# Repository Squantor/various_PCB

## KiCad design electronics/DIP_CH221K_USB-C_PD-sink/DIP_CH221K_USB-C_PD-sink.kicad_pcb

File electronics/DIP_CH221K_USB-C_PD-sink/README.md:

# DIP module CH221K USB-C PD sink
This is a USB-C PD sink using a CH221K chip in DIP format.
## TODO's
Still some things need to be done:
* Review with one night in between
* Produce at [Aisler](https://aisler.net/)
* Assemble
* Test & characterise
* update Readme.md with pictures and BOM
## BOM
 or LCSC
* CH221K USB-C PD sink
* USB-C connector PD only

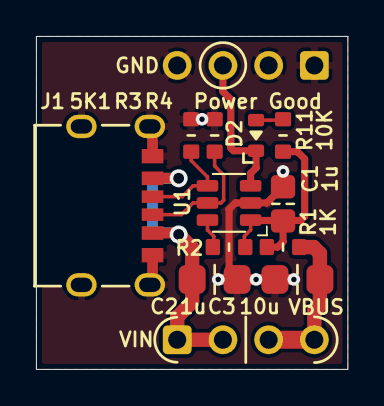
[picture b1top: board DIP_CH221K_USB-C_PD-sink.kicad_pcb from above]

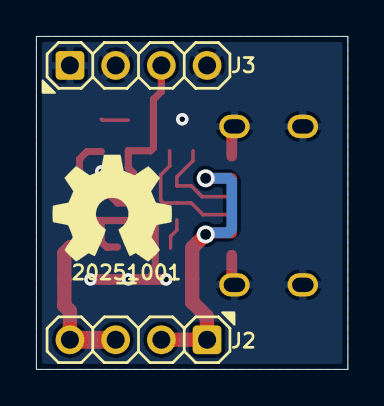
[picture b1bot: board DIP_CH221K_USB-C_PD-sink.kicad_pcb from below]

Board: 2 copper layers, 17.3 x 18.5 mm, 15 parts (4 on the bottom side), 9 nets.

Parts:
C1: 1u; C_0805+0603
C2: 1u; C_1206_0805
C3: 10u; C_1206_0805
D2: Power Good; LED_0603_hand
J1: USB-C_PD; USB-C-HRO-31-M-17_aisler
J2, J3: Conn_01x04; Header-0254-1X04-H010
N1: 20251001; Label_Generic
N2: OHWLOGO; OSHW-Symbol_6.7x6mm_SilkScreen
R1: 1K; R_0603_hand
R2: RSET; R_0603_hand
R3, R4: 5K1; R_0603_hand
R11: 10K; R_0603_hand
U1: CH221K; SOT23-6-HAND

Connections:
/CC1: J1.A5 (CC1), R3.1, U1.4 (CC1)
/CC2: J1.B5 (CC2), R4.1, U1.5 (CC2)
/PG: D2.1 (K), J3.3, U1.3 (PG)
/VBUS: C3.1, J2.3, J2.4, R1.1
/VDD: C1.2, R1.2, R2.2, R11.1, U1.1 (VDD)
/VIN: C2.1, J1.A9 (VBUS), J1.B9 (VBUS), J2.1, J2.2
GND: C1.1, C2.2, C3.2, J1.A12 (GND), J1.B12 (GND), J1.S (Shield), J3.1, J3.2, J3.4, R3.2, R4.2, U1.2 (GND)
unnamed: D2.2 (A), R11.2
unnamed: R2.1, U1.6 (CFG)

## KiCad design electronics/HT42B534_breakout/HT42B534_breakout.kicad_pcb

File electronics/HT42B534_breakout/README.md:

# Holtek HT42B534 breakout board
Breakout board for the [HT42B534-1](https://www.holtek.com/productdetail/-/vg/42B534-x) USB to serial converter. Advantage of the HT42B534 is that it enumerates as a USB CDC device, has programmable EEPROM on board and available in a few tiny packages.
## TODO's
Still some things need to be done:
* schematic entry
* PCB layout
* Review with one night in between (TODO)
* Produce at [OSHPARK](https://oshpark.com/) (TODO)
* Assemble (TODO)
* Test & characterise (TODO)
* update Readme.md with pictures and BOM (TODO)
## BOM
The HT42B534 can be hard to find but is available from [LCSC](https://lcsc.com/.
* HT42B534-1, [C95344 from LCSC](https://lcsc.com/product-detail/USB_HT42B534-MSOP-10_C95344.html)

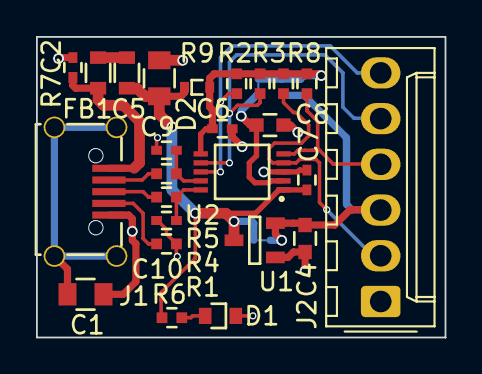
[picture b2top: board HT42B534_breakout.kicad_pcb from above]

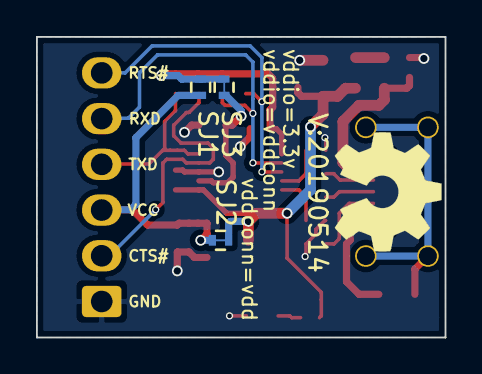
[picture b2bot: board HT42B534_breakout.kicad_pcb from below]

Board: 2 copper layers, 22.7 x 16.7 mm, 30 parts (5 on the bottom side), 18 nets.

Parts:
C1: 100n; C_0805
C2, C6, C7: 100n; C_0402
C4, C8: 1u; C_0603
C5: 10u; C_0805
C9, C10: 47p; C_0402
D1: RED; D_0603_hand
D2: D_Schottky; SOD-523
FB1: 600; R_0603_hand
J1: USB-ID; USB-muB-SMD_TH
J2: FTDI_PINS_1X06_input; Molex_KK-254_AE-6410-06A_1x06_P2.54mm_Vertical_FTDI_UART
N1: OHWLOGO; OSHW-Symbol_6.7x6mm_SilkScreen
N2: 20190514; Label_version
R1: 0; R_0402_hand
R2, R3, R8, R9: 10K; R_0402_hand
R4, R5: 33; R_0402_hand
R6: 1K; R_0402_hand
R7: Fuse; R_0603_hand
SJ1: vddio=vddconn; solder_jumper_2way_noconn
SJ2: vddconn=vdd; solder_jumper_2way_conn
SJ3: vddio=3.3v; solder_jumper_2way_conn
U1: MCP1702-CB; SOT23-3-Microchip-TT
U2: HT42B534-MSOP10; MSOP-10

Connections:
/CTSI: J2.2, R3.1, U2.4
/RTSO: J2.6, R9.1, U2.8
/RXI: J2.5, R2.1, U2.7
/TXO: J2.4, R8.1, U2.5
/USB_DM: J1.2, R5.1
/USB_DP: J1.3, R4.1
/VBUS: C2.1, J1.1, R7.2
/VDD: C5.1, C7.1, D2.1, FB1.1, R6.2, SJ2.2, U1.3, U2.1
/VDDCONN: C4.1, J2.3, SJ1.1, SJ2.1, U1.2
/VDDIO: C6.1, D2.2, R2.2, R3.2, R8.2, R9.2, SJ1.2, SJ3.1, U2.6
/VDD_33V: C8.1, SJ3.2, U2.2
/VSS: C1.2, C2.2, C4.2, C5.2, C6.2, C7.2, C8.2, C9.1, C10.1, D1.1, J1.5, J2.1, R1.2, U1.1, U2.3
unnamed: C1.1, J1.S
unnamed: C9.2, R5.2, U2.9
unnamed: C10.2, R4.2, U2.10
unnamed: D1.2, R6.1
unnamed: FB1.2, R7.1
unnamed: J1.4, R1.1

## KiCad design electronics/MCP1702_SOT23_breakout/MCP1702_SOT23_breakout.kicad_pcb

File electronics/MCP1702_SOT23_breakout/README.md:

# MCP1702 SOT23 breakout
Simple breakout for the SOT23 packaged MCP1702
## TODO's
Still some things need to be done:
* Produce at [OSHPARK](https://oshpark.com/shared_projects/U77scmmd) (WIP)
* Assemble (TODO)
* Test & characterise (TODO)
* update Readme.md with pictures and BOM (TODO)
## BOM
Due to the general shortage of passive components, where mentioned, just whatever you can find.
* [MCP1702](http://ww1.microchip.com/downloads/en/DeviceDoc/22008E.pdf)
Dual 0805/0603 footprint present to accomodate a few capacitor types.

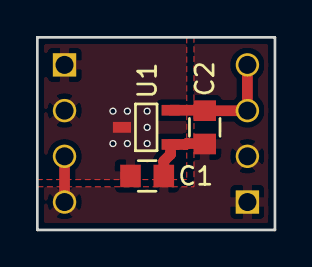
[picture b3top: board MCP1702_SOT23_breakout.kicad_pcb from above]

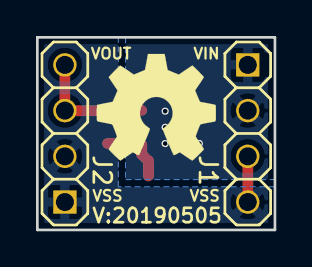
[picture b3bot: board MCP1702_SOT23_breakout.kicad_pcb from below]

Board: 2 copper layers, 13.2 x 10.7 mm, 7 parts (3 on the bottom side), 3 nets.

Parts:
C1, C2: TBD; C_0805+0603
J1: reference_input
J2: reference_output
N1: OHWLOGO; OSHW-Symbol_6.7x6mm_SilkScreen
N2: 20190505; Label_version
U1: MCP1702-CB; SOT23-3-Microchip-CB

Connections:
/VIN: C1.2, J1.1, J1.2, U1.3
/VOUT: C2.1, J2.3, J2.4, U1.2
/VSS: C1.1, C2.2, J1.3, J1.4, J2.1, J2.2, U1.1

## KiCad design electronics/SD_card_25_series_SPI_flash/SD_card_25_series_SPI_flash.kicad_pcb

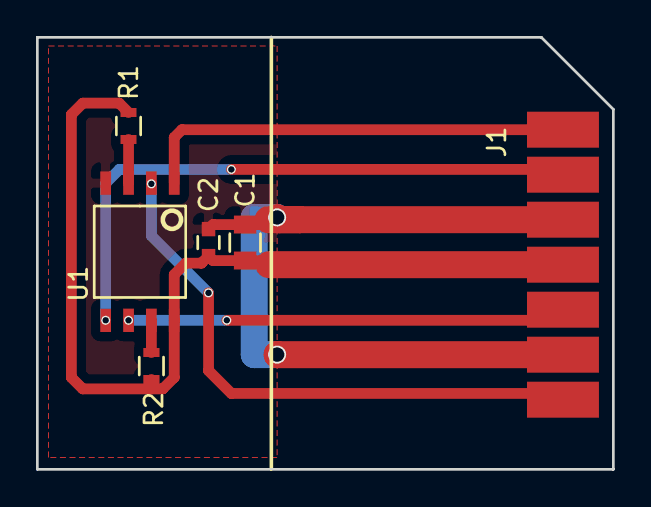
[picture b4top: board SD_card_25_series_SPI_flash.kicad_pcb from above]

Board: 2 copper layers, 32.0 x 24.0 mm, 6 parts (0 on the bottom side), 8 nets.

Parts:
C1: 1u; C_0805
C2: 100n; C_0603
J1: SD_CARD_connector
R1: 10K; R_0603
R2: 10k; R_0603
U1: W25Q32BV; W25Q32BVST

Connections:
+3V3: C1.1, C2.1, J1.4, R1.2, R2.1, U1.8
CS: J1.1, U1.1
DI: J1.2, U1.5
DO: J1.7, U1.2
GND: C1.2, C2.2, J1.3, J1.6, U1.4
unnamed: R1.1, U1.3
unnamed: R2.2, U1.7
SCLK: J1.5, U1.6

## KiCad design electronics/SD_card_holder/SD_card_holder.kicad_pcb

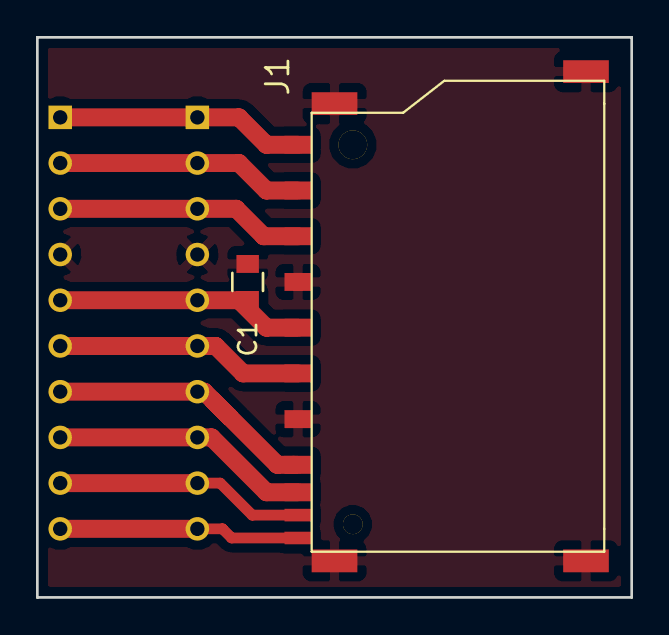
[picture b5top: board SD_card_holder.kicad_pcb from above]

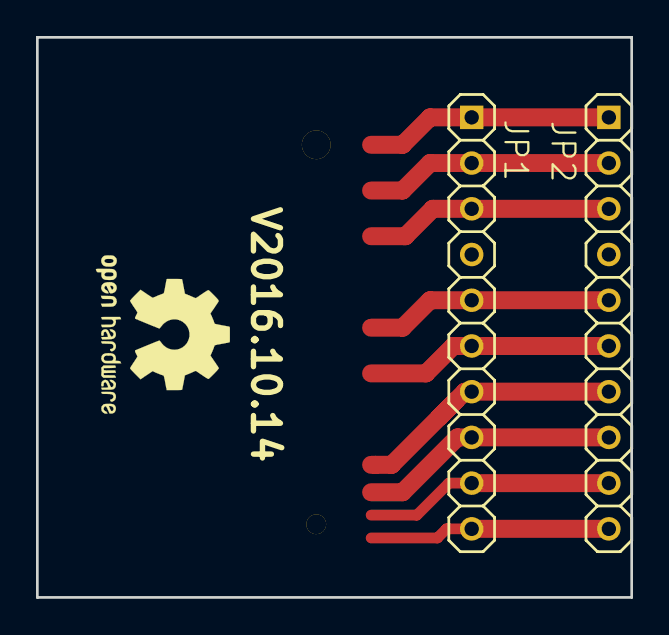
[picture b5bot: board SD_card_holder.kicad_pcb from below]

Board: 2 copper layers, 33.0 x 31.1 mm, 4 parts (2 on the bottom side), 10 nets.

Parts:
C1: 1u; C_0805
J1: SDCMF-10915W010; SquantorConnectors-SDCMF-10915W010
JP1, JP2: PINHD-1X10TH_NORMAL; SquantorConnectors-1X10_SMALL

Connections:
+3V3: C1.1, J1.4, JP1.5, JP2.5
GND: C1.2, J1.3, J1.6, J1.S1, J1.S2, J1.S3, J1.S4, JP1.4, JP2.4
unnamed: J1.1, JP1.2, JP2.2
unnamed: J1.2, JP1.3, JP2.3
unnamed: J1.5, JP1.6, JP2.6
unnamed: J1.7, JP1.7, JP2.7
unnamed: J1.8, JP1.8, JP2.8
unnamed: J1.9, JP1.1, JP2.1
unnamed: J1.CD, JP1.9, JP2.9
unnamed: J1.WP, JP1.10, JP2.10

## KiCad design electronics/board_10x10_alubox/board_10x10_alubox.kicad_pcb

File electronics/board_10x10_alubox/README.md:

# 4 module mainboard for 10*10cm aluminium box
Mainboard capable of fitting 4 5*4cm modules
# HSI (Hardware Software Interface)
TODO
## TODO's
Still some things need to be done:
* schematic entry 
* PCB layout
* Review with one night in between
* Produce at [OSHPARK](https://oshpark.com/)
* Assemble
* Test & characterise
* update Readme.md with pictures and BOM

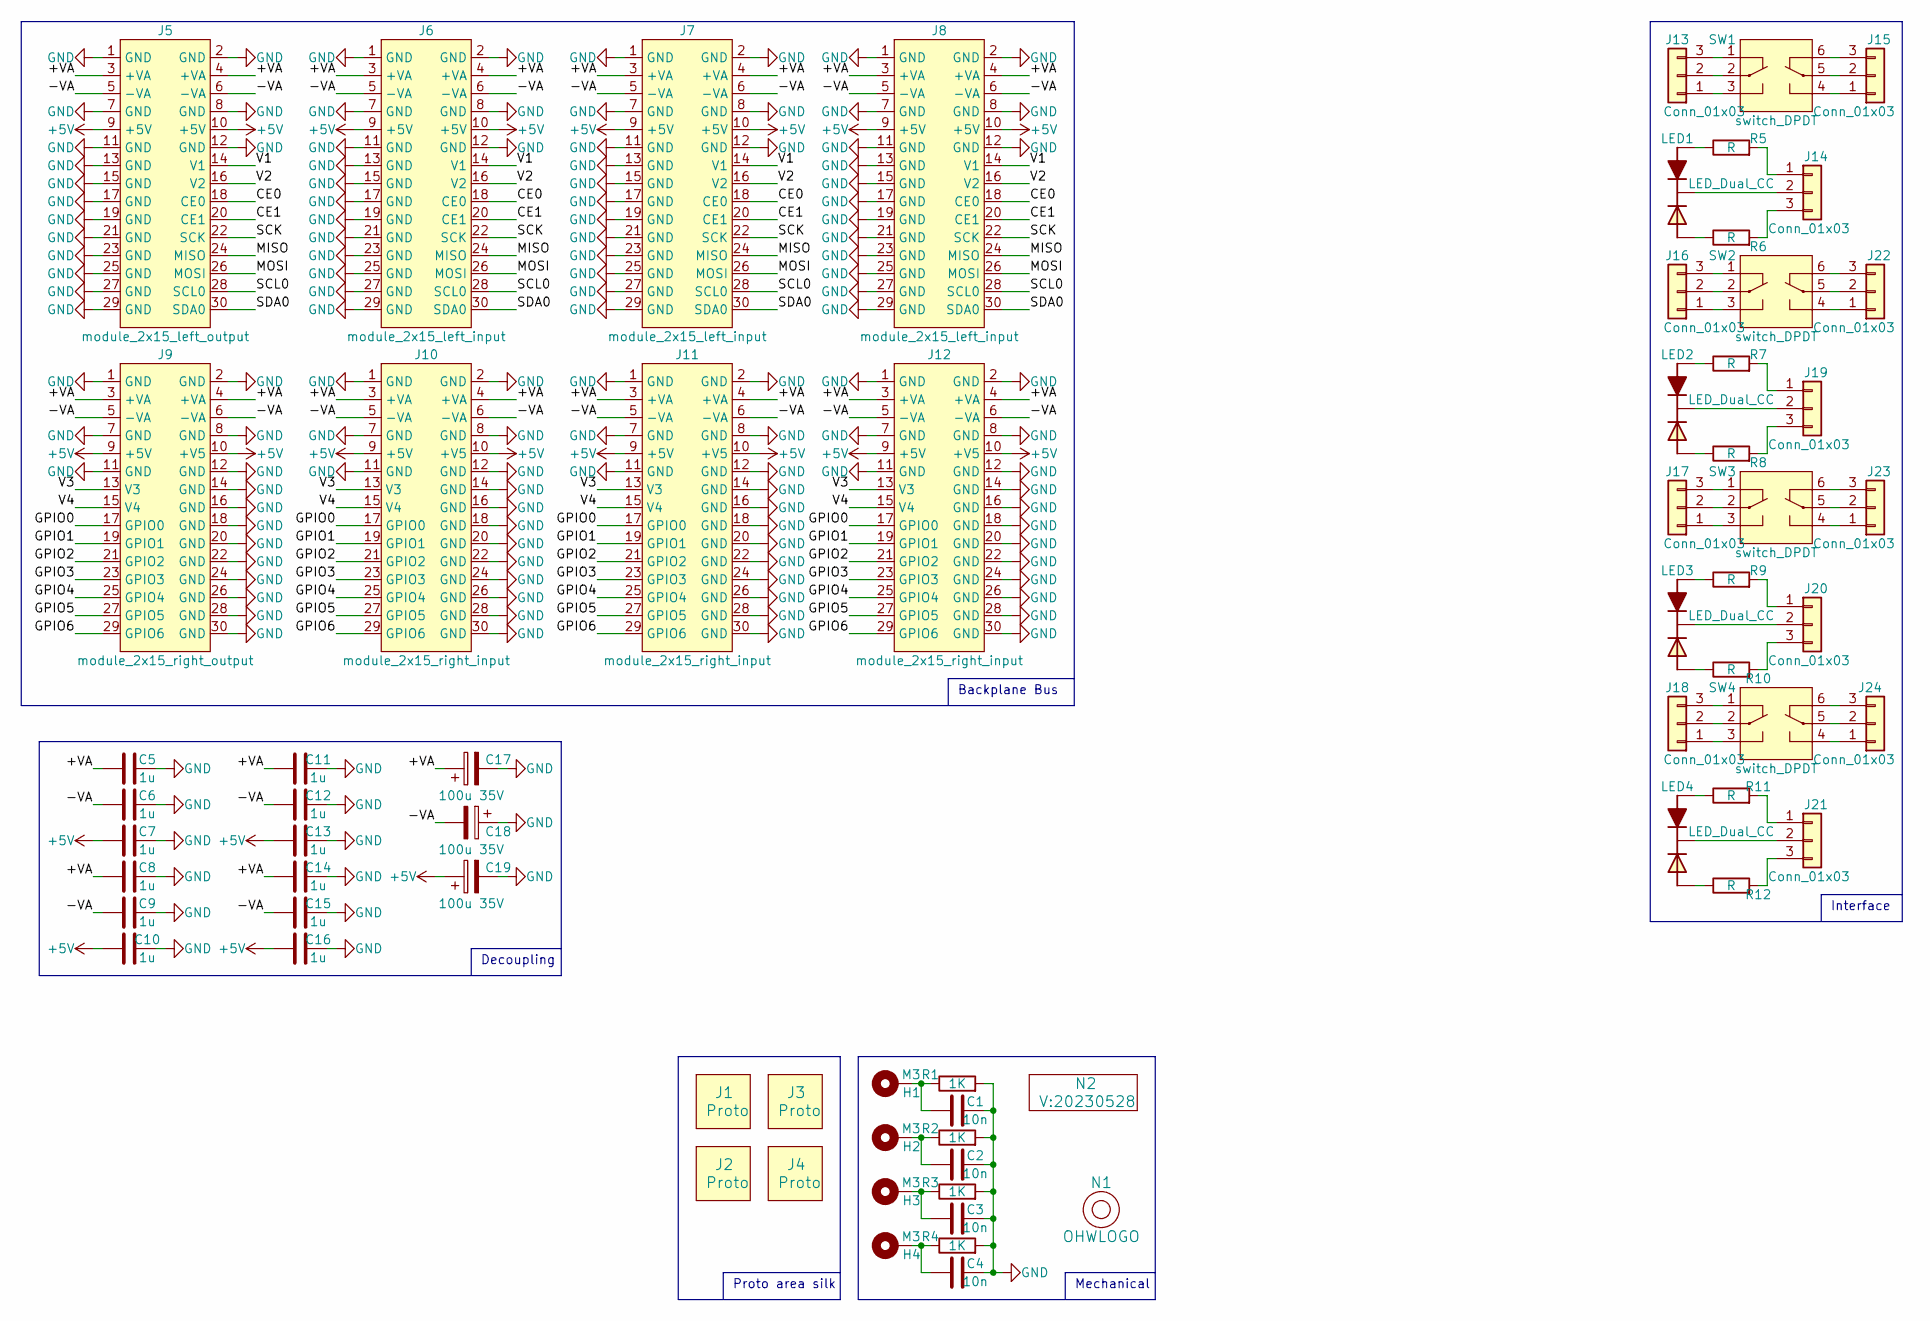
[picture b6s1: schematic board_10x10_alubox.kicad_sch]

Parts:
C1, C2, C3, C4: 10n; C_0805+0603
C5, C6, C7, C8, C9, C10, C11, C12, C13, C14, C15, C16: 1u; C_0805+0603
C17: 100u 35V; C-horizontal-035-080-200-elco-flipped
C18, C19: 100u 35V; C-horizontal-035-080-200-elco
H1, H2, H3, H4: M3; MountingHole_3.2mm_M3_Pad_Via
J1, J2, J3, J4: Proto; 4by4cm_module
J5: module_2x15_left_output; module_2x15_left
J6, J7, J8: module_2x15_left_input; module_2x15_left
J9: module_2x15_right_output; module_2x15_right
J10, J11, J12: module_2x15_right_input; module_2x15_right
J13, J14, J15, J16, J17, J18, J19, J20, J21, J22, J23, J24: Conn_01x03; JST_PH_B3B-PH-K_1x03_P2.00mm_Vertical
LED1, LED2, LED3, LED4: LED_Dual_CC; LED_DUAL_TH245_90deg
N1: OHWLOGO; OSHW-Symbol_6.7x6mm_SilkScreen
N2: V:20230528; Label_Generic
R1, R2, R3, R4: 1K; R_0805+0603
R5, R6, R7, R8, R9, R10, R11, R12: R; R_0603_hand
SW1, SW2, SW3, SW4: switch_DPDT; PS-22F02

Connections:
+5V: C7.1, C10.1, C13.1, C16.1, C19.1, J5.9 (+5V), J5.10 (+5V), J6.9 (+5V), J6.10 (+5V), J7.9 (+5V), J7.10 (+5V), J8.9 (+5V), J8.10 (+5V), J9.9 (+5V), J9.10 (+V5), J10.9 (+5V), J10.10 (+V5), J11.9 (+5V), J11.10 (+V5), J12.9 (+5V), J12.10 (+V5)
/+VA: C5.1, C8.1, C11.1, C14.1, C17.1, J5.3 (+VA), J5.4 (+VA), J6.3 (+VA), J6.4 (+VA), J7.3 (+VA), J7.4 (+VA), J8.3 (+VA), J8.4 (+VA), J9.3 (+VA), J9.4 (+VA), J10.3 (+VA), J10.4 (+VA), J11.3 (+VA), J11.4 (+VA), J12.3 (+VA), J12.4 (+VA)
/-VA: C6.1, C9.1, C12.1, C15.1, C18.2, J5.5 (-VA), J5.6 (-VA), J6.5 (-VA), J6.6 (-VA), J7.5 (-VA), J7.6 (-VA), J8.5 (-VA), J8.6 (-VA), J9.5 (-VA), J9.6 (-VA), J10.5 (-VA), J10.6 (-VA), J11.5 (-VA), J11.6 (-VA), J12.5 (-VA), J12.6 (-VA)
/CE0: J5.18 (CE0), J6.18 (CE0), J7.18 (CE0), J8.18 (CE0)
/CE1: J5.20 (CE1), J6.20 (CE1), J7.20 (CE1), J8.20 (CE1)
/GPIO0: J9.17 (GPIO0), J10.17 (GPIO0), J11.17 (GPIO0), J12.17 (GPIO0)
/GPIO1: J9.19 (GPIO1), J10.19 (GPIO1), J11.19 (GPIO1), J12.19 (GPIO1)
/GPIO2: J9.21 (GPIO2), J10.21 (GPIO2), J11.21 (GPIO2), J12.21 (GPIO2)
/GPIO3: J9.23 (GPIO3), J10.23 (GPIO3), J11.23 (GPIO3), J12.23 (GPIO3)
/GPIO4: J9.25 (GPIO4), J10.25 (GPIO4), J11.25 (GPIO4), J12.25 (GPIO4)
/GPIO5: J9.27 (GPIO5), J10.27 (GPIO5), J11.27 (GPIO5), J12.27 (GPIO5)
/GPIO6: J9.29 (GPIO6), J10.29 (GPIO6), J11.29 (GPIO6), J12.29 (GPIO6)
/MISO: J5.24 (MISO), J6.24 (MISO), J7.24 (MISO), J8.24 (MISO)
/MOSI: J5.26 (MOSI), J6.26 (MOSI), J7.26 (MOSI), J8.26 (MOSI)
/SCK: J5.22 (SCK), J6.22 (SCK), J7.22 (SCK), J8.22 (SCK)
/SCL0: J5.28 (SCL0), J6.28 (SCL0), J7.28 (SCL0), J8.28 (SCL0)
/SDA0: J5.30 (SDA0), J6.30 (SDA0), J7.30 (SDA0), J8.30 (SDA0)
/V1: J5.14 (V1), J6.14 (V1), J7.14 (V1), J8.14 (V1)
/V2: J5.16 (V2), J6.16 (V2), J7.16 (V2), J8.16 (V2)
/V3: J9.13 (V3), J10.13 (V3), J11.13 (V3), J12.13 (V3)
/V4: J9.15 (V4), J10.15 (V4), J11.15 (V4), J12.15 (V4)
GND: C1.2, C2.2, C3.2, C4.2, C5.2, C6.2, C7.2, C8.2, C9.2, C10.2, C11.2, C12.2, C13.2, C14.2, C15.2, C16.2, C17.2, C18.1, C19.2, J5.1 (GND), J5.2 (GND), J5.7 (GND), J5.8 (GND), J5.11 (GND), J5.12 (GND), J5.13 (GND), J5.15 (GND), J5.17 (GND), J5.19 (GND), J5.21 (GND), J5.23 (GND), J5.25 (GND), J5.27 (GND), J5.29 (GND), J6.1 (GND), J6.2 (GND), J6.7 (GND), J6.8 (GND), J6.11 (GND), J6.12 (GND), J6.13 (GND), J6.15 (GND), J6.17 (GND), J6.19 (GND), J6.21 (GND), J6.23 (GND), J6.25 (GND), J6.27 (GND), J6.29 (GND), J7.1 (GND), J7.2 (GND), J7.7 (GND), J7.8 (GND), J7.11 (GND), J7.12 (GND), J7.13 (GND), J7.15 (GND), J7.17 (GND), J7.19 (GND), J7.21 (GND), J7.23 (GND), J7.25 (GND), J7.27 (GND), J7.29 (GND), J8.1 (GND), J8.2 (GND), J8.7 (GND), J8.8 (GND), J8.11 (GND), J8.12 (GND), J8.13 (GND), J8.15 (GND), J8.17 (GND), J8.19 (GND), J8.21 (GND), J8.23 (GND), J8.25 (GND), J8.27 (GND), J8.29 (GND), J9.1 (GND), J9.2 (GND), J9.7 (GND), J9.8 (GND), J9.11 (GND), J9.12 (GND), J9.14 (GND), J9.16 (GND), J9.18 (GND), J9.20 (GND), J9.22 (GND), J9.24 (GND), J9.26 (GND), J9.28 (GND), J9.30 (GND), J10.1 (GND), J10.2 (GND), J10.7 (GND), J10.8 (GND), J10.11 (GND), J10.12 (GND), J10.14 (GND), J10.16 (GND), J10.18 (GND), J10.20 (GND), J10.22 (GND), J10.24 (GND), J10.26 (GND), J10.28 (GND), J10.30 (GND), J11.1 (GND), J11.2 (GND), J11.7 (GND), J11.8 (GND), J11.11 (GND), J11.12 (GND), J11.14 (GND), J11.16 (GND), J11.18 (GND), J11.20 (GND), J11.22 (GND), J11.24 (GND), J11.26 (GND), J11.28 (GND), J11.30 (GND), J12.1 (GND), J12.2 (GND), J12.7 (GND), J12.8 (GND), J12.11 (GND), J12.12 (GND), J12.14 (GND), J12.16 (GND), J12.18 (GND), J12.20 (GND), J12.22 (GND), J12.24 (GND), J12.26 (GND), J12.28 (GND), J12.30 (GND), R1.2, R2.2, R3.2, R4.2
unnamed: C1.1, H1.1, R1.1
unnamed: C2.1, H2.1, R2.1
unnamed: C3.1, H3.1, R3.1
unnamed: C4.1, H4.1, R4.1
unnamed: J13.1, SW1.3 (SW1_P2)
unnamed: J13.2, SW1.2 (SW1_C1)
unnamed: J13.3, SW1.1 (SW1_P1)
unnamed: J14.1, R5.2
unnamed: J14.2, LED1.2 (C)
unnamed: J14.3, R6.2
unnamed: J15.1, SW1.4 (SW2_P2)
unnamed: J15.2, SW1.5 (SW2_C1)
unnamed: J15.3, SW1.6 (SW2_P2)
unnamed: J16.1, SW2.3 (SW1_P2)
unnamed: J16.2, SW2.2 (SW1_C1)
unnamed: J16.3, SW2.1 (SW1_P1)
unnamed: J17.1, SW3.3 (SW1_P2)
unnamed: J17.2, SW3.2 (SW1_C1)
unnamed: J17.3, SW3.1 (SW1_P1)
unnamed: J18.1, SW4.3 (SW1_P2)
unnamed: J18.2, SW4.2 (SW1_C1)
unnamed: J18.3, SW4.1 (SW1_P1)
unnamed: J19.1, R7.2
unnamed: J19.2, LED2.2 (C)
unnamed: J19.3, R8.2
unnamed: J20.1, R9.2
unnamed: J20.2, LED3.2 (C)
unnamed: J20.3, R10.2
unnamed: J21.1, R11.2
unnamed: J21.2, LED4.2 (C)
unnamed: J21.3, R12.2
unnamed: J22.1, SW2.4 (SW2_P2)
unnamed: J22.2, SW2.5 (SW2_C1)
unnamed: J22.3, SW2.6 (SW2_P2)
unnamed: J23.1, SW3.4 (SW2_P2)
unnamed: J23.2, SW3.5 (SW2_C1)
unnamed: J23.3, SW3.6 (SW2_P2)
unnamed: J24.1, SW4.4 (SW2_P2)
unnamed: J24.2, SW4.5 (SW2_C1)
unnamed: J24.3, SW4.6 (SW2_P2)
unnamed: LED1.1 (A1), R5.1
unnamed: LED1.3 (A2), R6.1
unnamed: LED2.1 (A1), R7.1
unnamed: LED2.3 (A2), R8.1
unnamed: LED3.1 (A1), R9.1
unnamed: LED3.3 (A2), R10.1
unnamed: LED4.1 (A1), R11.1
unnamed: LED4.3 (A2), R12.1

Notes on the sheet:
Proto area silk
Decoupling
Interface
Mechanical
Backplane Bus

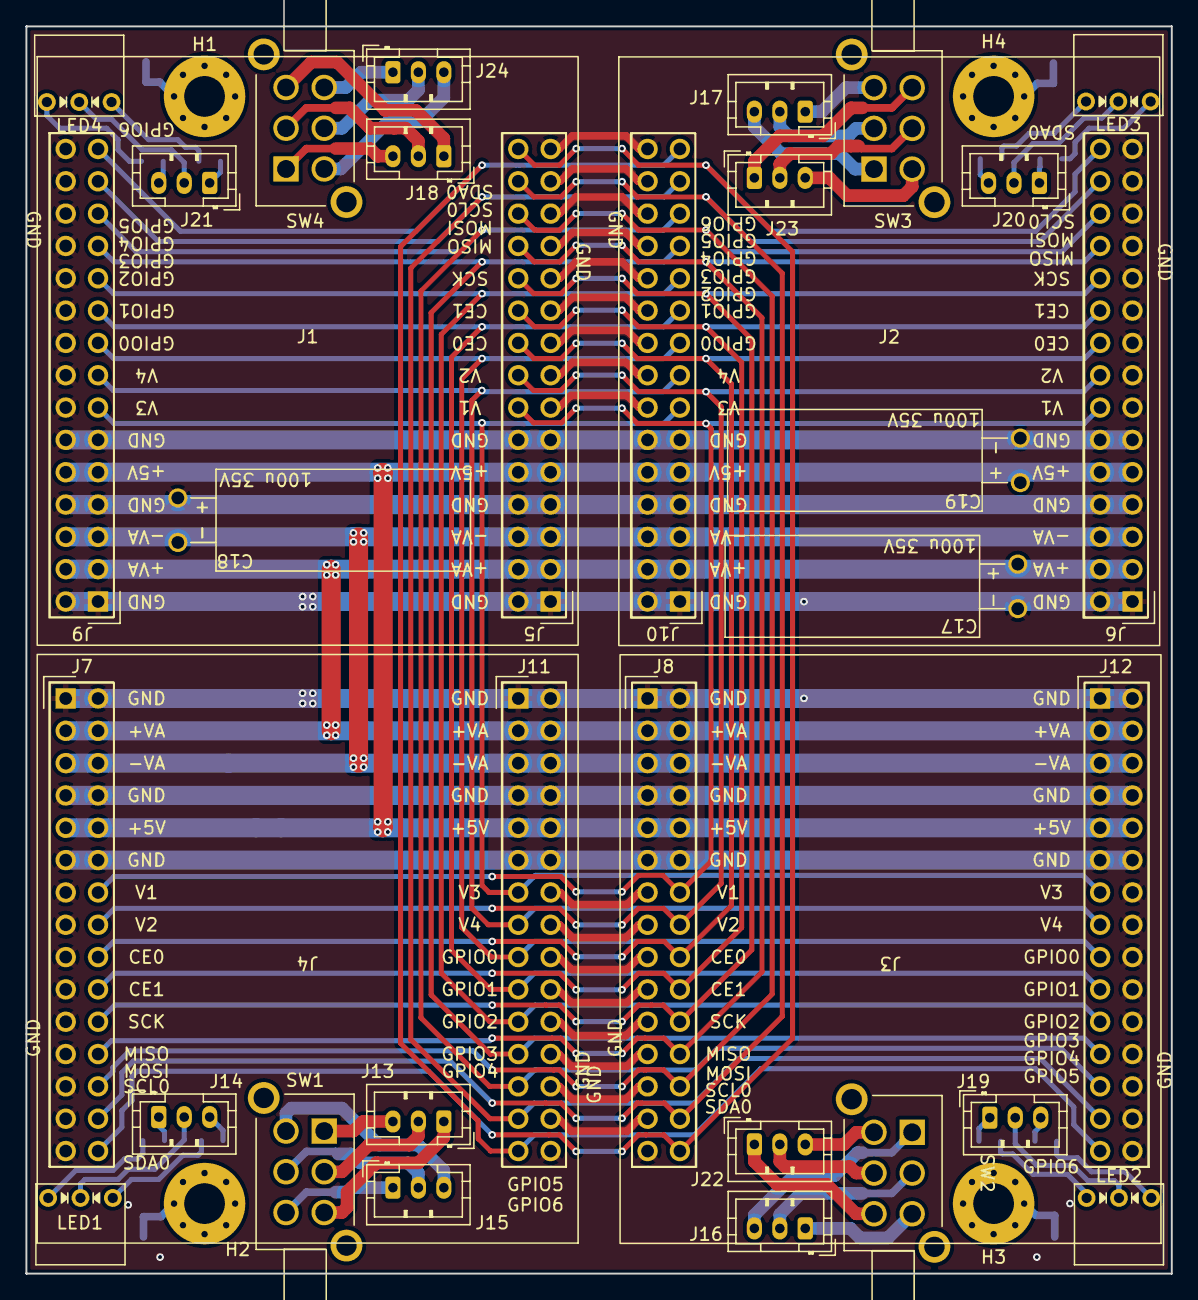
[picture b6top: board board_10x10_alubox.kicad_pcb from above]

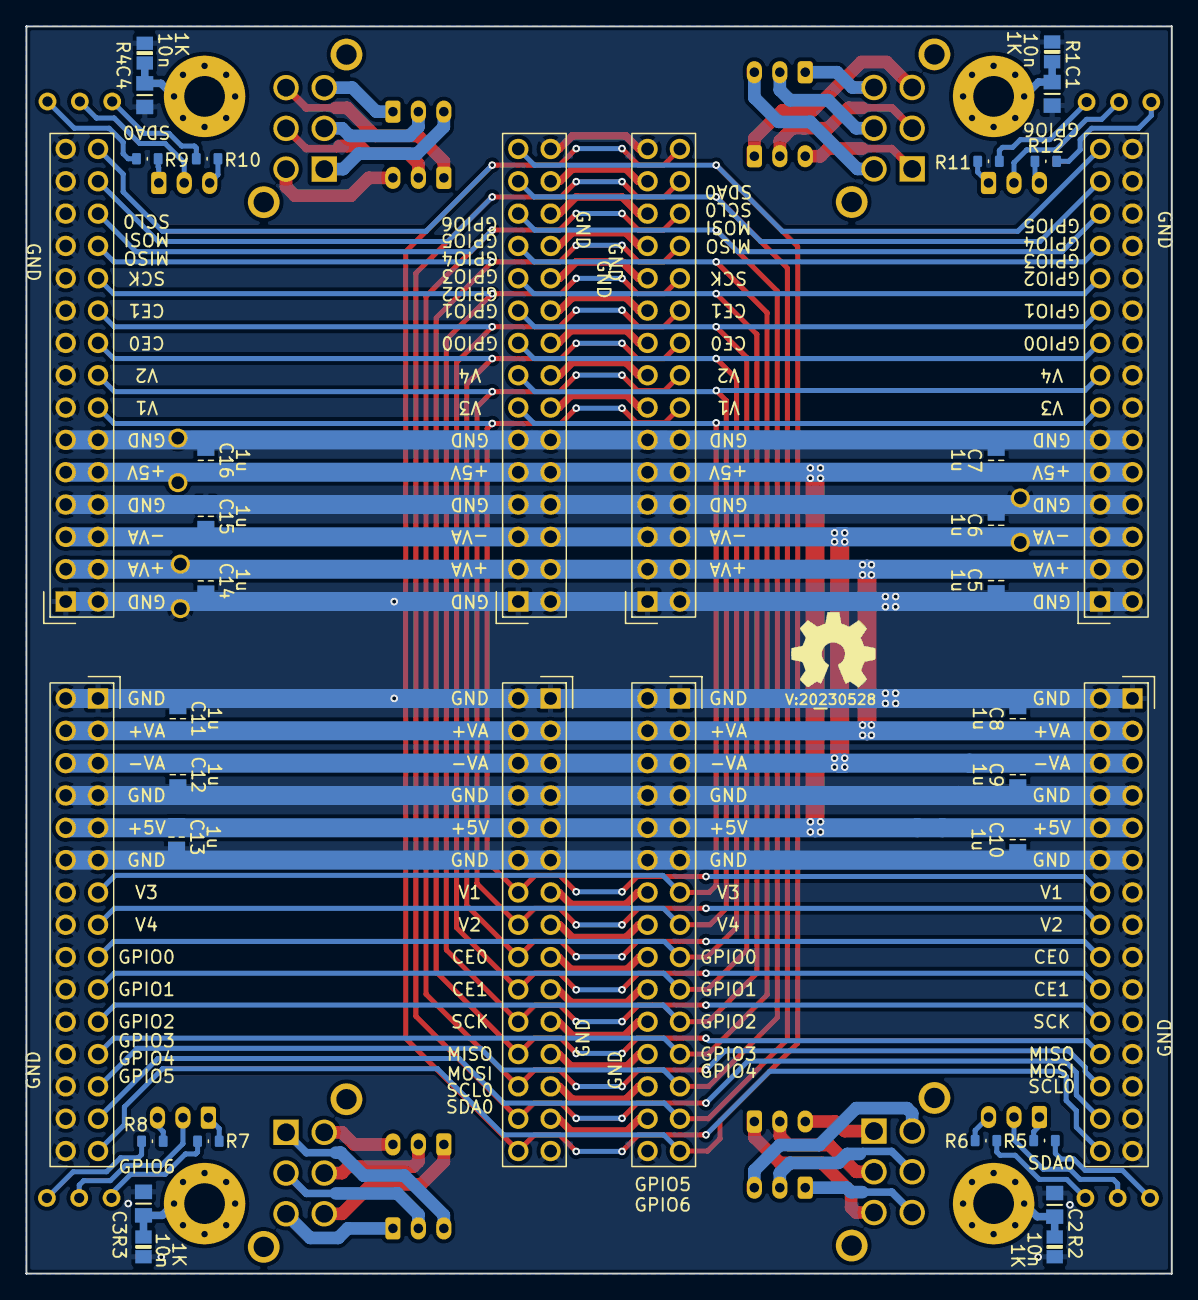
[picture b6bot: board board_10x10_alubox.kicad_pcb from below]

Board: 2 copper layers, 90.0 x 98.0 mm, 69 parts (30 on the bottom side), 70 nets.

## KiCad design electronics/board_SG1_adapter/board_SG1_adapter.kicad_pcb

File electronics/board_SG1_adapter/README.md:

# Strapubox SG1 adapter board template
baseline PCB for the [SG1 adapter box from strapubox](https://www.strapubox.de/wp-content/uploads/2021/06/MB21-0078_Strapubox_DB_Eurostecker_01.pdf).
## TODO's
Still some things need to be done:
* Review with one night in between
* Produce PCB
* Assemble
* Test & characterise
* update Readme.md with pictures and BOM
## BOM
* Standard transformer sizing

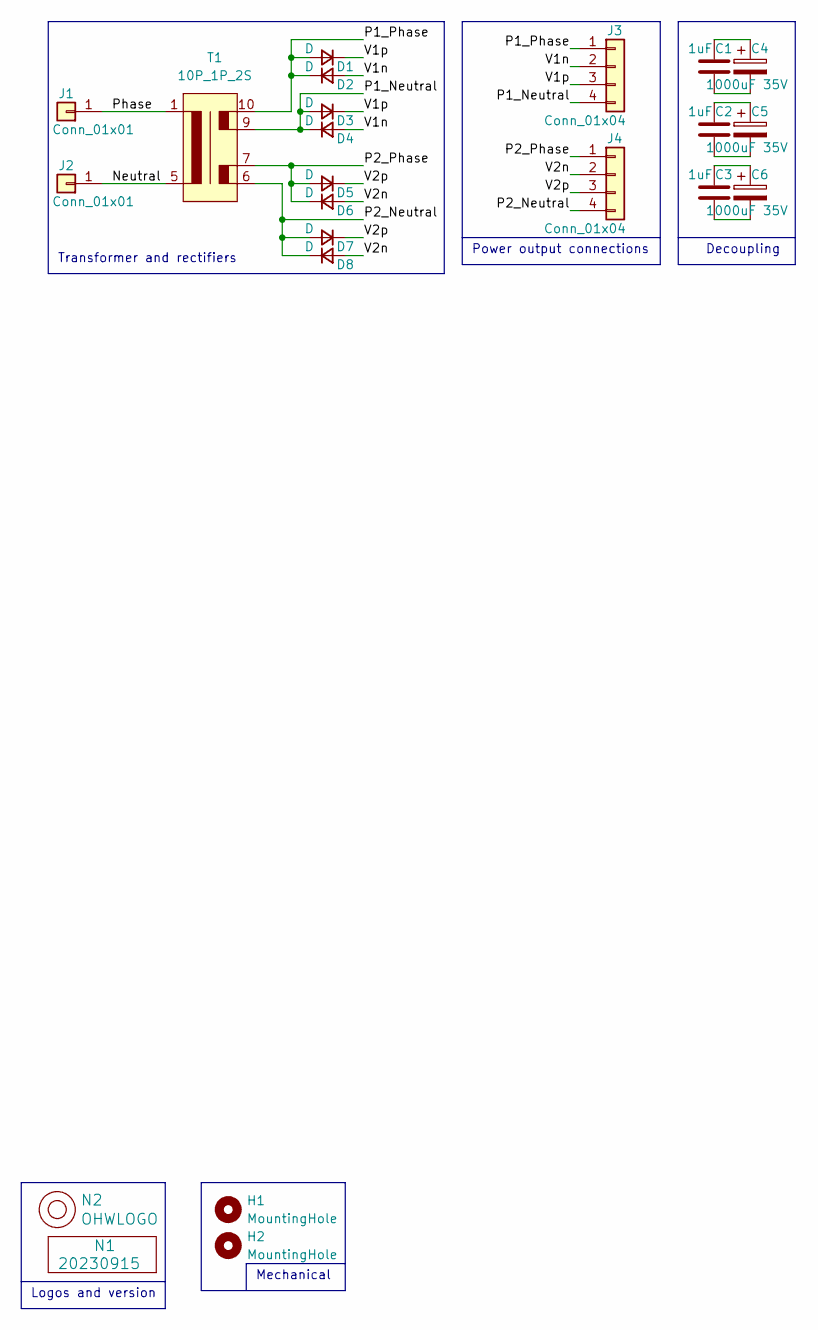
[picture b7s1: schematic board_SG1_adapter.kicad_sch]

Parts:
C1, C2, C3: 1uF; C_0805+0603
C4, C5, C6: 1000uF 35V; C-050-100-elco
D1, D2, D3, D4, D5, D6, D7, D8: D; D_SMB
H1, H2: MountingHole; MountingHole_2.2mm_M2
J1, J2: Conn_01x01; pad_power
J3, J4: Conn_01x04; JST_XH_B4B-XH-A_1x04_P2.50mm_Vertical
N1: 20230915; Label_Generic
N2: OHWLOGO; OSHW-Symbol_6.7x6mm_SilkScreen
T1: 10P_1P_2S; 10pin_5pitch_32x27_1Pri_2Sec

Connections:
/Neutral: J2.1, T1.5
/P1_Neutral: D3.2 (A), D4.1 (K), J3.4, T1.9
/P1_Phase: D1.2 (A), D2.1 (K), J3.1, T1.10
/P2_Neutral: D7.2 (A), D8.1 (K), J4.4, T1.6
/P2_Phase: D5.2 (A), D6.1 (K), J4.1, T1.7
/Phase: J1.1, T1.1
/V1n: D2.2 (A), D4.2 (A), J3.2
/V1p: D1.1 (K), D3.1 (K), J3.3
/V2n: D6.2 (A), D8.2 (A), J4.2
/V2p: D5.1 (K), D7.1 (K), J4.3
unnamed: C1.1, C4.1
unnamed: C1.2, C4.2
unnamed: C2.1, C5.1
unnamed: C2.2, C5.2
unnamed: C3.1, C6.1
unnamed: C3.2, C6.2

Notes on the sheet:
Power output connections
Decoupling
Logos and version
Transformer and rectifiers
Mechanical

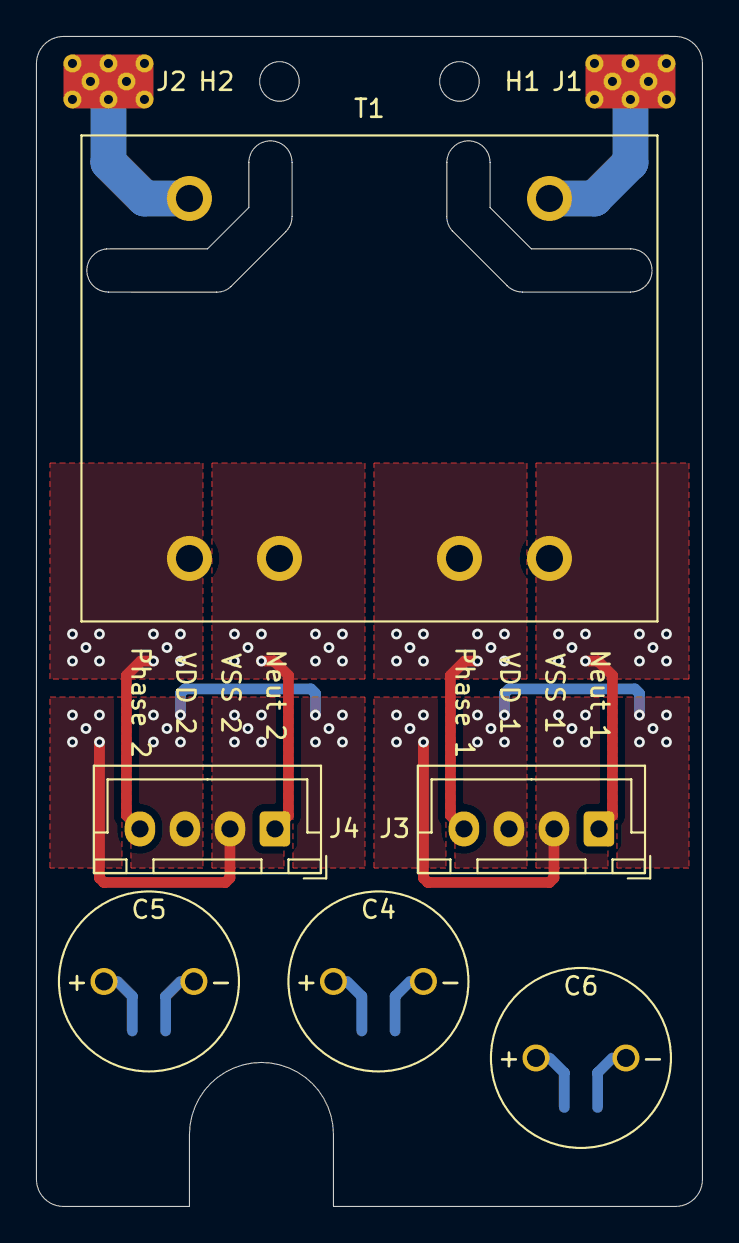
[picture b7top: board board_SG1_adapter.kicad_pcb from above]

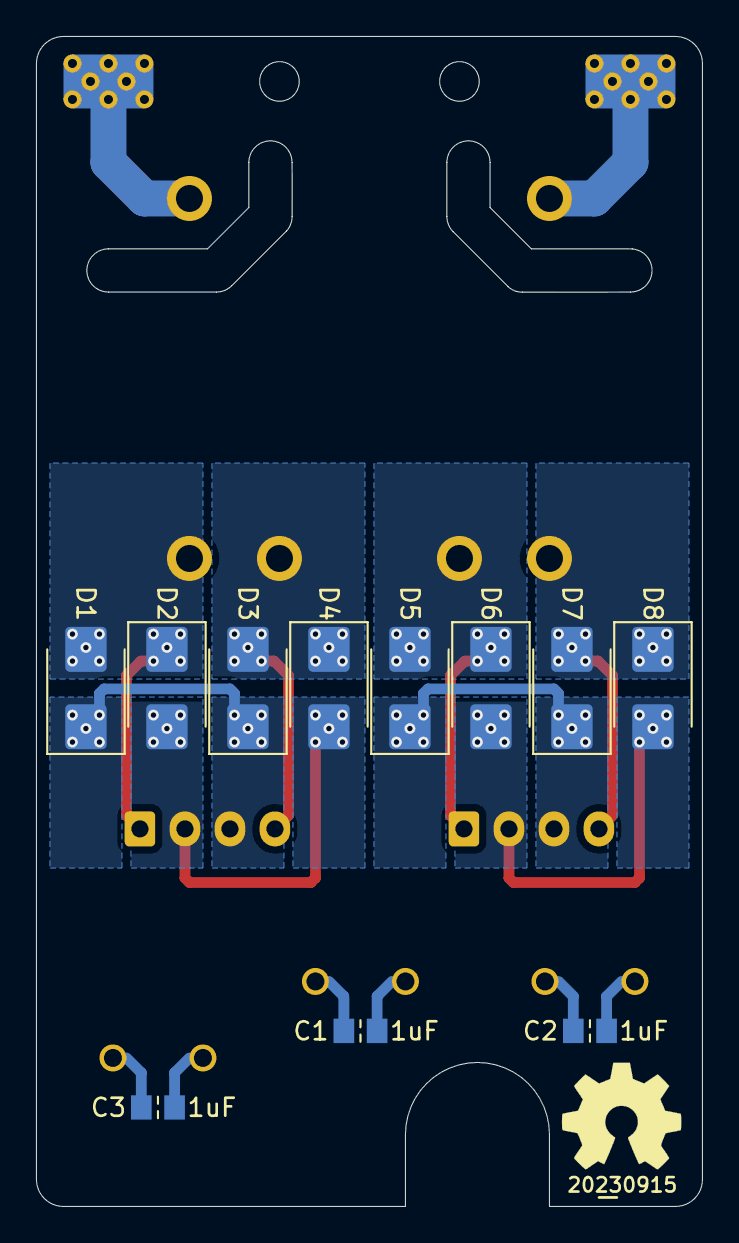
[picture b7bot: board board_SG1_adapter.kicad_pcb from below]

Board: 2 copper layers, 37.0 x 65.0 mm, 23 parts (13 on the bottom side), 16 nets.

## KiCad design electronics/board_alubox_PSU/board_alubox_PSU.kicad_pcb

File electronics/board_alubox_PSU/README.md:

# 10x10cm alubox module powersupply
4 by 5cm module with powersupply components. Two AC inputs one for a symmetrical powersupply and one for a single ended powersupply. Symmetric powersupply accepts LM317/LM337 regulators. Single ended supply has footprints for a LM317 regulator and LM78XX style regulators. All regulators are TO220 with a small heatsink. Due to limited space for capacitance the amount of current is also limited.
## TODO's
Still some things need to be done:
* schematic entry (WIP)
* PCB layout
* Review with one night in between
* Produce at [OSHPARK](https://oshpark.com/)
* Assemble
* Test & characterise
* update Readme.md with pictures and BOM
## BOM
This is a list of hardware components. If just mentioned a generic component like a 1K 0402 resistor, just name it as such, free to substitute. If you need some special integrated IC's show some sources like Mouser, Digikey, Farnell, or LCSC
* TO220 LM317, LM337, LM78XX style regulator
* SMA cased diodes
* Very skinny capacitors but substitute for your own
* 500mA trip polyfuses

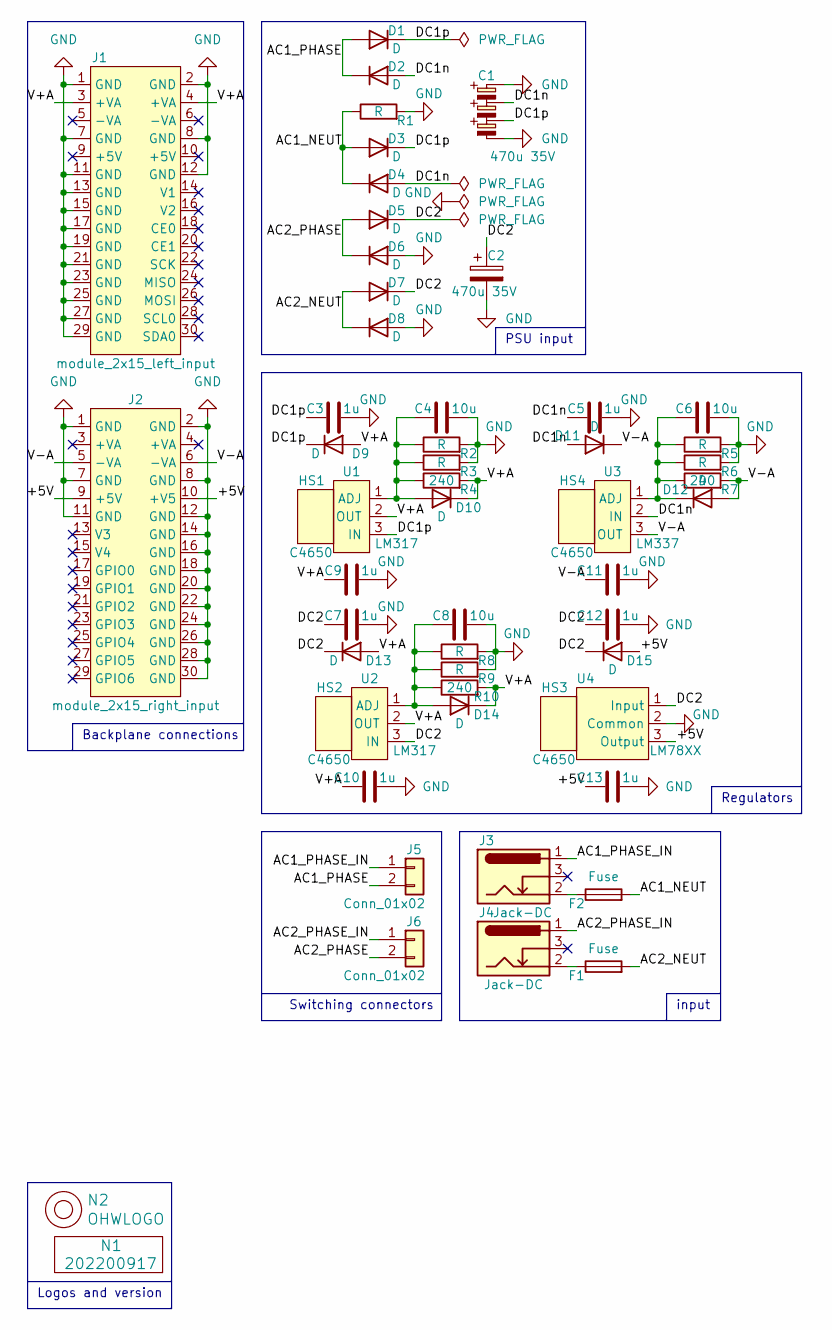
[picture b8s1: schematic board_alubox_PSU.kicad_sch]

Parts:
C1: 470u 35V; Cx3-035-080-elco
C2: 470u 35V; C-035-080-elco
C3, C5, C7, C9, C10, C11, C12, C13: 1u; C_0805+0603
C4, C6, C8: 10u; C_0805+0603
D1, D2, D3, D4, D5, D6, D7, D8, D9, D11, D13, D15: D; SOD-123F-hand
D10, D12, D14: D; SOD-523_hand
F1, F2: Fuse; F_1812-bourns
HS1, HS2, HS3, HS4: C4650; XSD_C4650
J1: module_2x15_left_input; module_2x15_left
J2: module_2x15_right_input; module_2x15_right
J3, J4: Jack-DC; BarrelJack_Horizontal_Holed
J5, J6: Conn_01x02; JST_PH_B2B-PH-K_1x02_P2.00mm_Vertical
N1: 202200917; Label_Generic
N2: OHWLOGO; OSHW-Symbol_6.7x6mm_SilkScreen
R1: R; R_1206
R2, R3, R5, R6, R8, R9: R; R_0805+0603
R4, R7, R10: 240; R_0805+0603
U1, U2: LM317; TO-220-3_Vertical
U3: LM337; TO-220-3_Vertical
U4: LM78XX; TO-220-3_Vertical

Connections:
/+5V: C13.1, D15.2 (A), J2.9 (+5V), J2.10 (+V5), U4.3 (Output)
/AC1_NEUT: D3.2 (A), D4.1 (K), F2.2, R1.1
/AC1_PHASE: D1.2 (A), D2.1 (K), J5.2
/AC1_PHASE_IN: J3.1, J5.1
/AC2_NEUT: D7.2 (A), D8.1 (K), F1.2
/AC2_PHASE: D5.2 (A), D6.1 (K), J6.2
/AC2_PHASE_IN: J4.1, J6.1
/DC1n: C1.2, C5.1, D2.2 (A), D4.2 (A), D11.2 (A), U3.2 (IN)
/DC1p: C1.3, C3.1, D1.1 (K), D3.1 (K), D9.1 (K), U1.3 (IN)
/DC2: C2.1, C7.1, C12.1, D5.1 (K), D7.1 (K), D13.1 (K), D15.1 (K), U2.3 (IN), U4.1 (Input)
/V+A: C9.1, C10.1, D9.2 (A), D10.1 (K), D13.2 (A), D14.1 (K), J1.3 (+VA), J1.4 (+VA), R4.2, R10.2, U1.2 (OUT), U2.2 (OUT)
/V-A: C11.1, D11.1 (K), D12.2 (A), J2.5 (-VA), J2.6 (-VA), R7.2, U3.3 (OUT)
GND: C1.1, C1.4, C2.2, C3.2, C4.2, C5.2, C6.2, C7.2, C8.2, C9.2, C10.2, C11.2, C12.2, C13.2, D6.2 (A), D8.2 (A), J1.1 (GND), J1.2 (GND), J1.7 (GND), J1.8 (GND), J1.11 (GND), J1.12 (GND), J1.13 (GND), J1.15 (GND), J1.17 (GND), J1.19 (GND), J1.21 (GND), J1.23 (GND), J1.25 (GND), J1.27 (GND), J1.29 (GND), J2.1 (GND), J2.2 (GND), J2.7 (GND), J2.8 (GND), J2.11 (GND), J2.12 (GND), J2.14 (GND), J2.16 (GND), J2.18 (GND), J2.20 (GND), J2.22 (GND), J2.24 (GND), J2.26 (GND), J2.28 (GND), J2.30 (GND), R1.2, R2.2, R3.2, R5.2, R6.2, R8.2, R9.2, U4.2 (Common)
unnamed: C4.1, D10.2 (A), R2.1, R3.1, R4.1, U1.1 (ADJ)
unnamed: C6.1, D12.1 (K), R5.1, R6.1, R7.1, U3.1 (ADJ)
unnamed: C8.1, D14.2 (A), R8.1, R9.1, R10.1, U2.1 (ADJ)
unnamed: F1.1, J4.2
unnamed: F2.1, J3.2

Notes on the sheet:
Backplane connections
input
Logos and version
PSU input
Switching connectors
Regulators

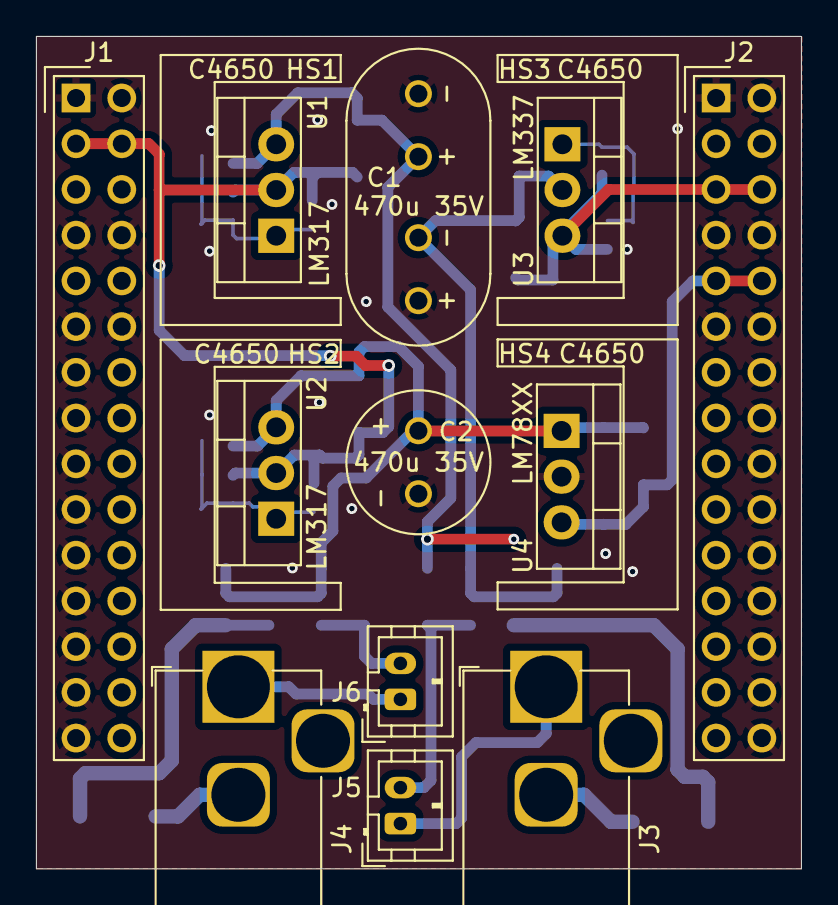
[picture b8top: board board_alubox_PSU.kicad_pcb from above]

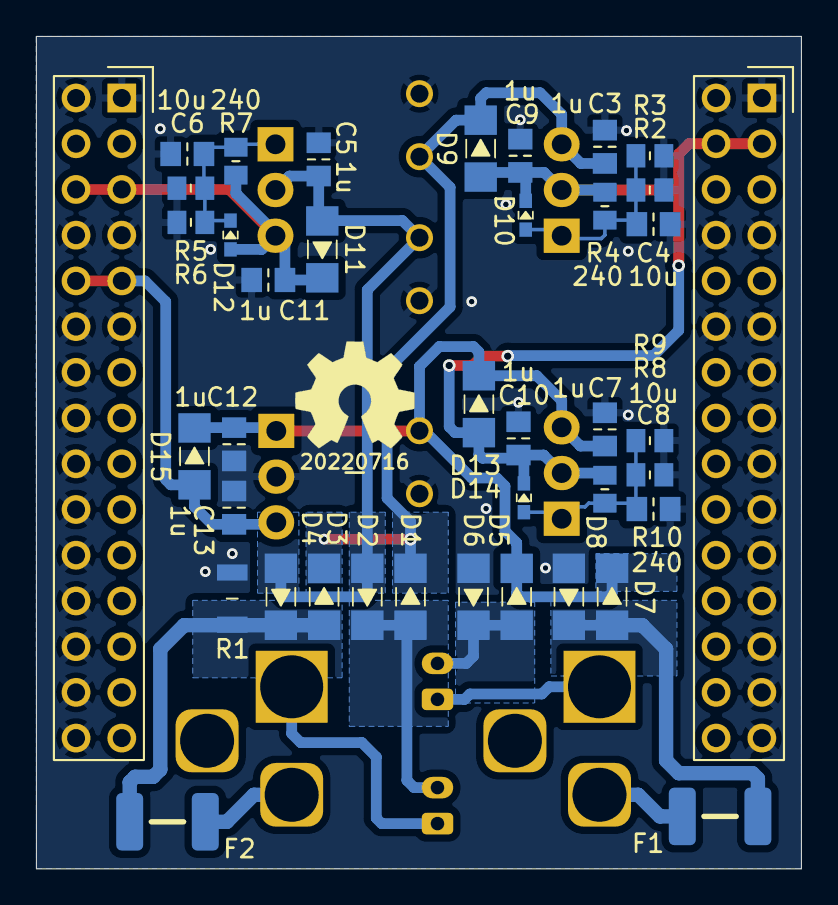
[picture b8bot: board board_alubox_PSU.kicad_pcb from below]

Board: 2 copper layers, 42.5 x 46.2 mm, 56 parts (40 on the bottom side), 18 nets.
